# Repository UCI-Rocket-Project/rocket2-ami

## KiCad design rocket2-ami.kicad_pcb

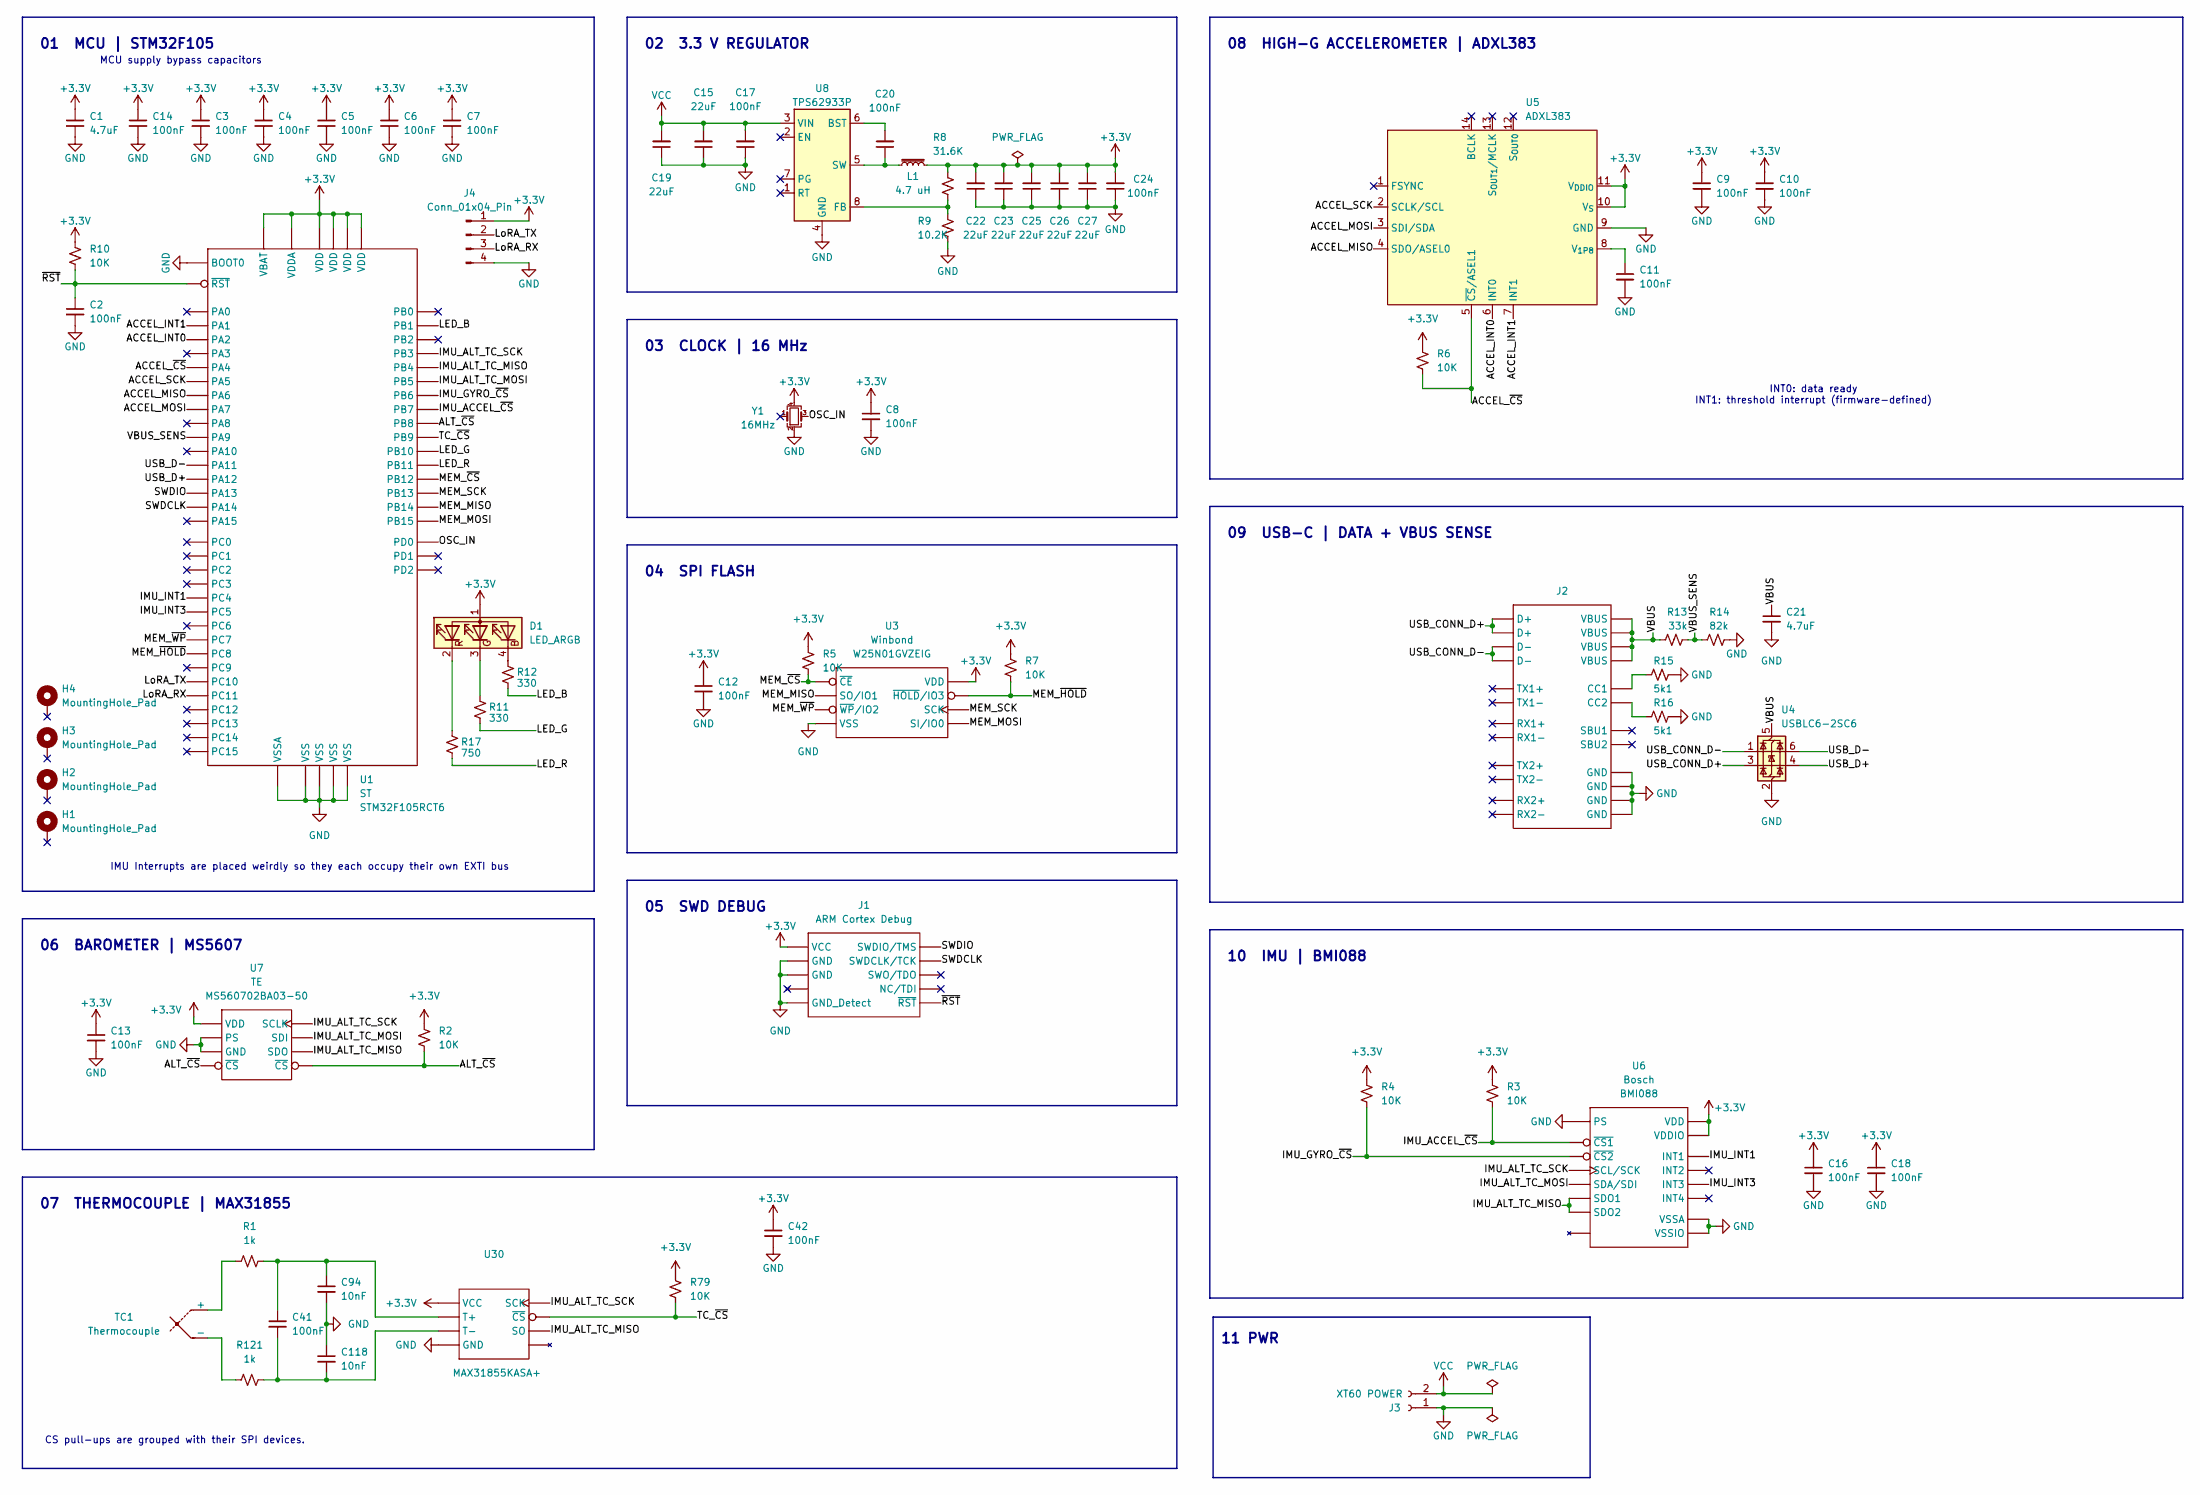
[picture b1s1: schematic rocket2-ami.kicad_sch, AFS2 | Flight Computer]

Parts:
C1: 4.7uF; C_0603_1608Metric; Part # Generic 4.7uF 6.3V X7R 0603 MLCC
C2, C3, C4, C5, C6, C7, C8, C9, C10, C11, C12, C13, C14, C16, C18, C20, C24: 100nF; C_0603_1608Metric; Part # Generic 0603 6.3V 100nF X7R MLCC
C15, C19: 22uF; C_0603_1608Metric; Part # Generic 0603 16V 22uF X5R MLCC
C17: 100nF; C_0603_1608Metric; Part # Generic 0603 50V 100nF X7R MLCC
C21: 4.7uF; C_0603_1608Metric; Part # Generic 0603 6.3V 4.7uF X7R MLCC
C22, C23, C25, C26, C27: 22uF; C_0603_1608Metric; Part # Generic 0603 6.3V 22uF X5R MLCC
C41, C42: 100nF; C_0402_1005Metric; Part # GRM155R71H104KE14D
C94, C118: 10nF; C_0402_1005Metric; Part # GRM155R71H103KA88D
D1: LED_ARGB; LED RGB (0606) APTF1616LSEEZGKQBKC
H1, H2, H3, H4: MountingHole_Pad; MountingHole_3.2mm_M3_Pad_Via
J1: ARM Cortex Debug; PinHeader_2x05_P1.27mm_Vertical_SMD
J2: USB_C_Receptacle_GCT_USB4105-xx-A_16P_TopMnt_Horizontal; Part # USB4105-GF-A
J3: XT60 POWER; AMASS_XT60PW-M_1x02_P7.20mm_Horizontal; Part # Generic Horizontal TH P5.08mm Screw Fas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
J4: Conn_01x04_Pin; PinHeader_1x04_P2.54mm_Vertical
L1: 4.7 uH; Inductor (4.7uH) IND_03-4R7-R_EAT
R1, R121: 1k; R_0402_1005Metric; Part # RC0402FR-071KL
R2, R3, R4, R5, R6, R7, R10, R79: 10K; R_0402_1005Metric; Part # RC0402FR-0710KL
R8: 31.6K; R_0402_1005Metric
R9: 10.2K; R_0402_1005Metric; Part # Generic RES SMD 10K OHM 1% 1/16W 0402
R11, R12: 330; R_0402_1005Metric; Part # RC0402FR-07330RL
R13: 33k; R_0603_1608Metric; Part # RC0603FR-0733KL
R14: 82k; R_0603_1608Metric; Part # RC0603FR-0782KL
R15, R16: 5k1; R_0603_1608Metric; Part # CRCW06035K10FKEA
R17: 750; R_0402_1005Metric; Part # RC0402FR-07750RL
TC1: Thermocouple; TC_Connector AM-K-PCB; Part # AM-K-PCB
U1: STM32F105RCT6; MCU STM32F105RCT6; Part # STM32F105RCT6
U3: WSON-8-1EP_8x6mm_P1.27mm_EP3.4x4.3mm; Part # W25N01GVZEIG
U4: USBLC6-2SC6; SOT-23-6
U5: ADXL383; 14_LGA
U6: IMU BMI088; Part # BMI088
U7: Altimeter MS5607-02BA; Part # MS560702BA03-50
U8: TPS62933P; SOT-583-8
U30: SOIC-8_3.9x4.9mm_P1.27mm; Part # MAX31855KASA+
Y1: 16MHz; Crystal_SMD_2016-4Pin_2.0x1.6mm; Part # ECS-1633-160-BN-TR

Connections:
+3.3V: C1.1, C3.1, C4.1, C5.1, C6.1, C7.1, C8.1, C9.1, C10.1, C12.1, C13.1, C14.1, C16.1, C18.1, C22.2, C23.2, C24.2, C25.2, C26.2, C27.2, C42.1, D1.1 (A), J1.1 (VCC), J4.1, L1.2, R2.1, R3.1, R4.1, R5.1, R6.1, R7.1, R8.1, R10.1, R79.1, U1.1 (VBAT), U1.13 (VDDA), U1.19 (VDD), U1.32 (VDD), U1.48 (VDD), U1.64 (VDD), U3.8 (VDD), U5.10 (V_{S}), U5.11 (V_{DDIO}), U6.3 (VDD), U6.11 (VDDIO), U7.1 (VDD), U30.4 (VCC), Y1.4
/ACCEL_INT0: U1.16 (PA2), U5.6 (INT0)
/ACCEL_INT1: U1.15 (PA1), U5.7 (INT1)
/ACCEL_MISO: U1.22 (PA6), U5.4 (SDO/ASEL0)
/ACCEL_MOSI: U1.23 (PA7), U5.3 (SDI/SDA)
/ACCEL_SCK: U1.21 (PA5), U5.2 (SCLK/SCL)
/ACCEL_~CS: R6.2, U1.20 (PA4), U5.5 (~CS/ASEL1)
/ALT_~CS: R2.2, U1.61 (PB8), U7.4 (~CS), U7.5 (~CS)
/IMU_ACCEL_~CS: R3.2, U1.59 (PB7), U6.14 (~CS1)
/IMU_ALT_TC_MISO: U1.56 (PB4), U6.10 (SDO2), U6.15 (SDO1), U7.6 (SDO), U30.7 (SO)
/IMU_ALT_TC_MOSI: U1.57 (PB5), U6.9 (SDA/SDI), U7.7 (SDI)
/IMU_ALT_TC_SCK: U1.55 (PB3), U6.8 (SCL/SCK), U7.8 (SCLK), U30.5 (SCK)
/IMU_GYRO_~CS: R4.2, U1.58 (PB6), U6.5 (~CS2)
/IMU_INT1: U1.24 (PC4), U6.16 (INT1)
/IMU_INT3: U1.25 (PC5), U6.12 (INT3)
/LED_B: R12.2, U1.27 (PB1)
/LED_G: R11.2, U1.29 (PB10)
/LED_R: R17.2, U1.30 (PB11)
/LoRA_RX: J4.3, U1.52 (PC11)
/LoRA_TX: J4.2, U1.51 (PC10)
/MEM_MISO: U1.35 (PB14), U3.2 (SO/IO1)
/MEM_MOSI: U1.36 (PB15), U3.5 (SI/IO0)
/MEM_SCK: U1.34 (PB13), U3.6 (SCK)
/MEM_~CS: R5.2, U1.33 (PB12), U3.1 (~CE)
/MEM_~HOLD: R7.2, U1.39 (PC8), U3.7 (~HOLD/IO3)
/MEM_~WP: U1.38 (PC7), U3.3 (~WP/IO2)
/OSC_IN: U1.5 (PD0), Y1.3
/SWDCLK: J1.4 (SWDCLK/TCK), U1.49 (PA14)
/SWDIO: J1.2 (SWDIO/TMS), U1.46 (PA13)
/TC_~CS: R79.2, U1.62 (PB9), U30.6 (~CS)
/USB_CONN_D+: J2.A6 (D+), J2.B6 (D+), U4.3 (I/O2)
/USB_CONN_D-: J2.A7 (D-), J2.B7 (D-), U4.1 (I/O1)
/USB_D+: U1.45 (PA12), U4.4 (I/O2)
/USB_D-: U1.44 (PA11), U4.6 (I/O1)
/VBUS: C21.1, J2.A4 (VBUS), J2.A9 (VBUS), J2.B4 (VBUS), J2.B9 (VBUS), R13.1, U4.5 (VBUS)
/VBUS_SENS: R13.2, R14.2, U1.42 (PA9)
/~RST: C2.1, J1.10 (~RST), R10.2, U1.7 (~RST)
GND: C1.2, C2.2, C3.2, C4.2, C5.2, C6.2, C7.2, C8.2, C9.2, C10.2, C11.2, C12.2, C13.2, C14.2, C15.1, C16.2, C17.1, C18.2, C19.1, C21.2, C22.1, C23.1, C24.1, C25.1, C26.1, C27.1, C42.2, C94.2, C118.1, J1.3 (GND), J1.5 (GND), J1.9 (GND_Detect), J2.A1 (GND), J2.A12 (GND), J2.B1 (GND), J2.B12 (GND), J3.1, J4.4, R9.2, R14.1, R15.1, R16.1, U1.12 (VSSA), U1.18 (VSS), U1.31 (VSS), U1.47 (VSS), U1.60 (BOOT0), U1.63 (VSS), U3.4 (VSS), U4.2 (GND), U5.9 (GND), U6.4 (VSSA), U6.6 (VSSIO), U6.7 (PS), U7.2 (PS), U7.3 (GND), U8.4 (GND), U30.1 (GND), Y1.2 (G)
unnamed: D1.4 (BK), R12.1
unnamed: D1.3 (GK), R11.1
unnamed: D1.2 (RK), R17.1
unnamed: J2.A5 (CC1), R15.2
unnamed: J2.B5 (CC2), R16.2
unnamed: R1.1, TC1.1 (+)
unnamed: R121.1, TC1.2 (-)
unnamed: C11.1, U5.8 (V_{1P8})
unnamed: C20.2, U8.6 (BST)
unnamed: R8.2, R9.1, U8.8 (FB)
unnamed: C20.1, L1.1, U8.5 (SW)
unnamed: C41.1, C94.1, R1.2, U30.3 (T+)
unnamed: C41.2, C118.2, R121.2, U30.2 (T-)
VCC: C15.2, C17.2, C19.2, J3.2, U8.3 (VIN)

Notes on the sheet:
IMU Interrupts are placed weirdly so they each occupy their own EXTI bus
07 THERMOCOUPLE | MAX31855
10 IMU | BMI088
MCU supply bypass capacitors
02 3.3 V REGULATOR
05 SWD DEBUG
09 USB-C | DATA + VBUS SENSE
03 CLOCK | 16 MHz
INT0: data ready INT1: threshold interrupt (firmware-defined)
06 BAROMETER | MS5607
04 SPI FLASH
11 PWR
01 MCU | STM32F105
08 HIGH-G ACCELEROMETER | ADXL383
CS pull-ups are grouped with their SPI devices.

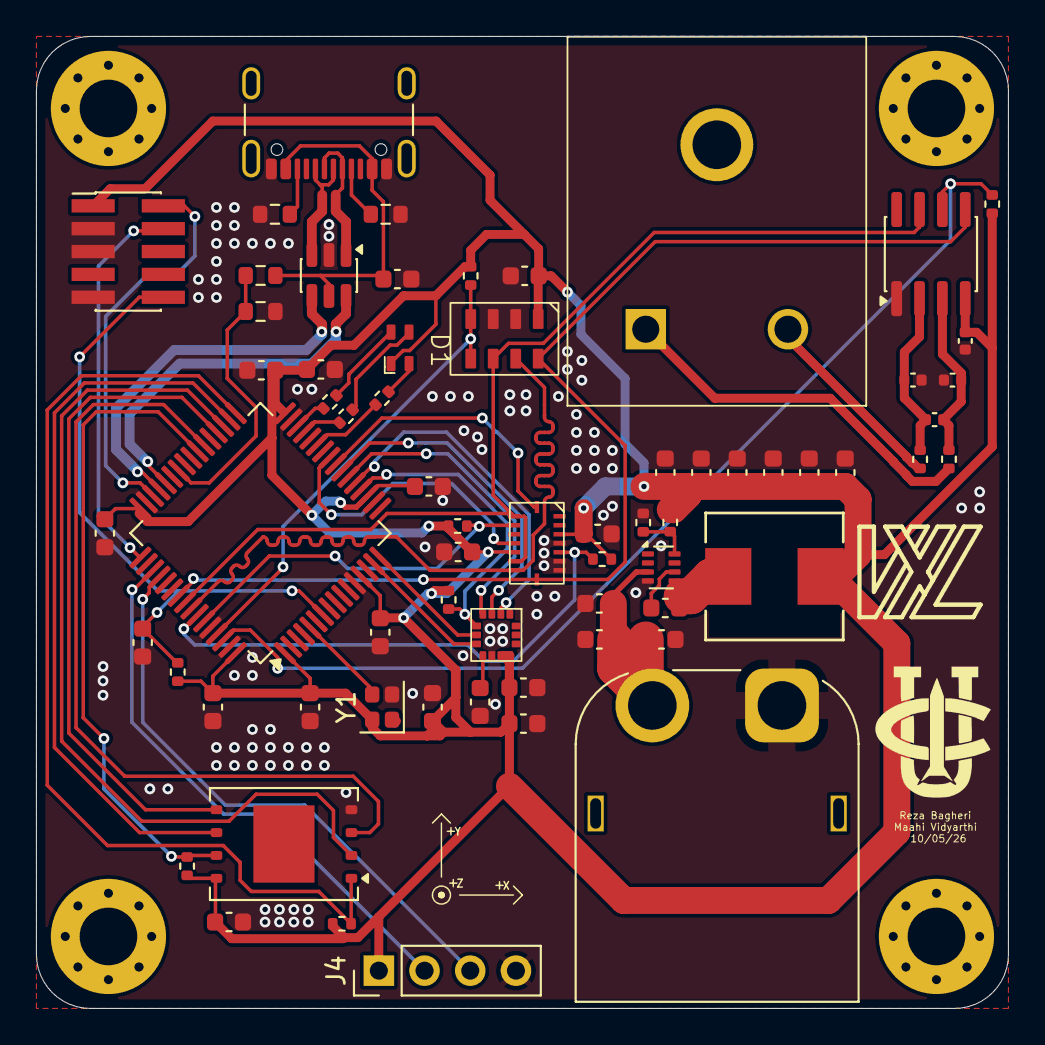
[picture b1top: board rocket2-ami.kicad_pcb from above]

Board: 2 copper layers, 54.0 x 54.0 mm, 70 parts (0 on the bottom side), 52 nets.

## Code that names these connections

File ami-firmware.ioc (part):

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Mcu.Name=STM32F105R(8-B-C)Tx
Mcu.Package=LQFP64
Mcu.UserName=STM32F105RCTx
PA1.GPIOParameters=GPIO_Label
PA1.GPIO_Label=ACCEL_INT1
PA1.Signal=GPXTI1
PA11.Mode=Device_Only
PA11.Signal=USB_OTG_FS_DM
PA12.Mode=Device_Only
PA12.Signal=USB_OTG_FS_DP
PA13.Mode=Serial_Wire
PA13.Signal=SYS_JTMS-SWDIO
PA14.Mode=Serial_Wire
PA14.Signal=SYS_JTCK-SWCLK
PA2.GPIOParameters=GPIO_Label
PA2.GPIO_Label=ACCEL_INT0
PA2.Signal=GPXTI2
PA4.GPIOParameters=GPIO_Label
PA4.GPIO_Label=ACCEL_nCS
PA4.Signal=GPIO_Output
PA5.GPIOParameters=GPIO_Label
PA5.GPIO_Label=ACCEL_SCK
PA5.Mode=Full_Duplex_Master
PA5.Signal=SPI1_SCK
PA6.GPIOParameters=GPIO_Label
PA6.GPIO_Label=ACCEL_MISO
PA6.Mode=Full_Duplex_Master
PA6.Signal=SPI1_MISO
PA7.GPIOParameters=GPIO_Label
PA7.GPIO_Label=ACCEL_MOSI
PA7.Mode=Full_Duplex_Master
PA7.Signal=SPI1_MOSI
PA9.Signal=GPIO_Input
PB1.GPIOParameters=GPIO_Label
PB1.GPIO_Label=LED_B
PB1.Signal=S_TIM3_CH4
PB10.GPIOParameters=GPIO_Label
PB10.GPIO_Label=LED_G
PB10.Signal=S_TIM2_CH3
PB11.GPIOParameters=GPIO_Label
PB11.GPIO_Label=LED_R
PB11.Signal=S_TIM2_CH4
PB12.GPIOParameters=PinState,GPIO_Label
PB12.GPIO_Label=MEM_nCS
PB12.PinState=GPIO_PIN_SET
PB12.Signal=GPIO_Output
PB13.GPIOParameters=GPIO_Label
PB13.GPIO_Label=MEM_SCK
PB13.Mode=Full_Duplex_Master
PB13.Signal=SPI2_SCK
PB14.GPIOParameters=GPIO_Label
PB14.GPIO_Label=MEM_MISO
PB14.Mode=Full_Duplex_Master
PB14.Signal=SPI2_MISO
PB15.GPIOParameters=GPIO_Label
PB15.GPIO_Label=MEM_MOSI
PB15.Mode=Full_Duplex_Master
PB15.Signal=SPI2_MOSI
PB3.GPIOParameters=GPIO_Label
PB3.GPIO_Label=IMU_ALT_SCK
PB3.Mode=Full_Duplex_Master
PB3.Signal=SPI3_SCK
PB4.GPIOParameters=GPIO_Label
PB4.GPIO_Label=IMU_ALT_MISO
PB4.Mode=Full_Duplex_Master
PB4.Signal=SPI3_MISO
PB5.GPIOParameters=GPIO_Label
PB5.GPIO_Label=IMU_ALT_MOSI
PB5.Mode=Full_Duplex_Master
PB5.Signal=SPI3_MOSI
PB6.GPIOParameters=GPIO_Label
PB6.GPIO_Label=IMU_GYRO_nCS
PB6.Signal=GPIO_Output
PB7.GPIOParameters=GPIO_Label
PB7.GPIO_Label=IMU_ACCEL_nCS
PB7.Signal=GPIO_Output
PB8.GPIOParameters=GPIO_Label
PB8.GPIO_Label=ALT_nCS
PB8.Signal=GPIO_Output
PB9.GPIOParameters=GPIO_Label
PB9.GPIO_Label=TC_nCS
PB9.Signal=GPIO_Output
PC10.GPIOParameters=GPIO_Label
PC10.GPIO_Label=LoRa_TX
PC10.Mode=Asynchronous
PC10.Signal=UART4_TX
PC11.GPIOParameters=GPIO_Label
PC11.GPIO_Label=LoRa_RX
PC11.Mode=Asynchronous
PC11.Signal=UART4_RX
PC4.GPIOParameters=GPIO_Label
PC4.GPIO_Label=IMU_INT1
PC4.Signal=GPXTI4
PC5.GPIOParameters=GPIO_Label
PC5.GPIO_Label=IMU_INT3
PC5.Signal=GPXTI5
PC7.GPIOParameters=PinState,GPIO_Label
PC7.GPIO_Label=MEM_nWP
PC7.PinState=GPIO_PIN_SET
PC7.Signal=GPIO_Output
PC8.GPIOParameters=PinState,GPIO_Label
PC8.GPIO_Label=MEM_nHOLD
PC8.PinState=GPIO_PIN_SET
PC8.Signal=GPIO_Output
PD0-OSC_IN.Mode=HSE-External-Clock-Source
PD0-OSC_IN.Signal=RCC_OSC_IN
PD1-OSC_OUT.Mode=HSE-External-Clock-Source
PD1-OSC_OUT.Signal=RCC_OSC_OUT
RCC.HSEDivPLL=RCC_HSE_PREDIV_DIV2
RCC.HSE_VALUE=16000000
RCC.SYSCLKFreq_VALUE=72000000
RCC.SYSCLKSource=RCC_SYSCLKSOURCE_PLLCLK
board=custom
